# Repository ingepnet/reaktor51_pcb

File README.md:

# Reaktor51 kretskort for loddeøving

# #1 Reaktor51 LED

# #2 Reaktor51 Memory Game

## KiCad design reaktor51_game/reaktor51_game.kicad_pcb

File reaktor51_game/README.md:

# Reaktor51 Memory Game

Her er kort #2 i "Reaktor51" serien! Litt flere komponenter å lodde opp, men alt er enkle hullmonterte komponenter. Dette er et minnespill, der målet er å huske møsteret som blir vist med lyd og lys. Knappene har innebygde LED's som blinker i en tilfeldig rekkefølge. Spilleren må herme dette mønsteret ved å trykke på knappene. Lyd og lys indikerer om spilleren har tapt eller vunnet!

Det er valgt å bruke knapper med røde LED's. Disse lyser sterkest av de fargene som var tilgjengelig for denne typen knapper.

## Kretskort

Gerber for bestilling av PCB:
[./rev2/reaktor51_game_pcb_rev2.zip](./rev2/reaktor51_game_pcb_rev2.zip)

 - Loddestopplakk: Rød
 - Silketrykk: Hvit
 - Tykkelse: 1.6mm
 - Overflate: HASL lead free

## Deleliste

| Komponent | Beskrivelse                              | Antall   | Verdi           | Link   |
|-|-|-|-|-|
| BT1       | Batteriholder for CR2032                 | 1        | Keystone 103    | https://www.digikey.no/en/products/detail/keystone-electronics/103/331620       | 
| U1        | AVR Microkontroller                      | 1        | ATtiny13A-PU    | https://www.digikey.no/en/products/detail/microchip-technology/ATTINY13A-PU/1914671       | 
| C1, C2    | Keramisk kondensator                     | 2        | 1uF 25V         | https://www.digikey.no/en/products/detail/tdk-corporation/FG18X7R1E105KRT00/7326658      |
| LS1       | Piezo høyttaler D=14mm H=4mm Pitch=7.5mm | 1        | 14x4mm 7.5mm    | https://www.aliexpress.com/item/1005004932492920.html    |
| R1, R2, R3, R4, R6  | Motstand 150ohm (2.3x6mm)      | 5        | 150ohm          | https://www.digikey.no/en/products/detail/stackpole-electronics-inc/CF14JT150R/1741294    |
| R5        | Motstand 4.7kohm (2.3x6mm)               | 1        | 4.7kohm         | https://www.digikey.no/en/products/detail/stackpole-electronics-inc/CF14JT4K70/1741428    |
| SW1, SW2, SW3, SW4  | Trykknapp med rød LED 12x12mm  | 4        | 12x12x7.3 RED   | https://www.aliexpress.com/item/1005003507477622.html    |

## Skjema

## Håndtak

Bruk denne filen for å 3d-printe et håndtak, som gjør kortet behagelig å holde i. Printes i normal og speilvendt utgave. Klipp komponentbeina korte på undersiden, slik at håndtakene blir enklere å skyve innpå.

[./rev2/reaktor51_game_handle.step](./rev2/reaktor51_game_handle.step)

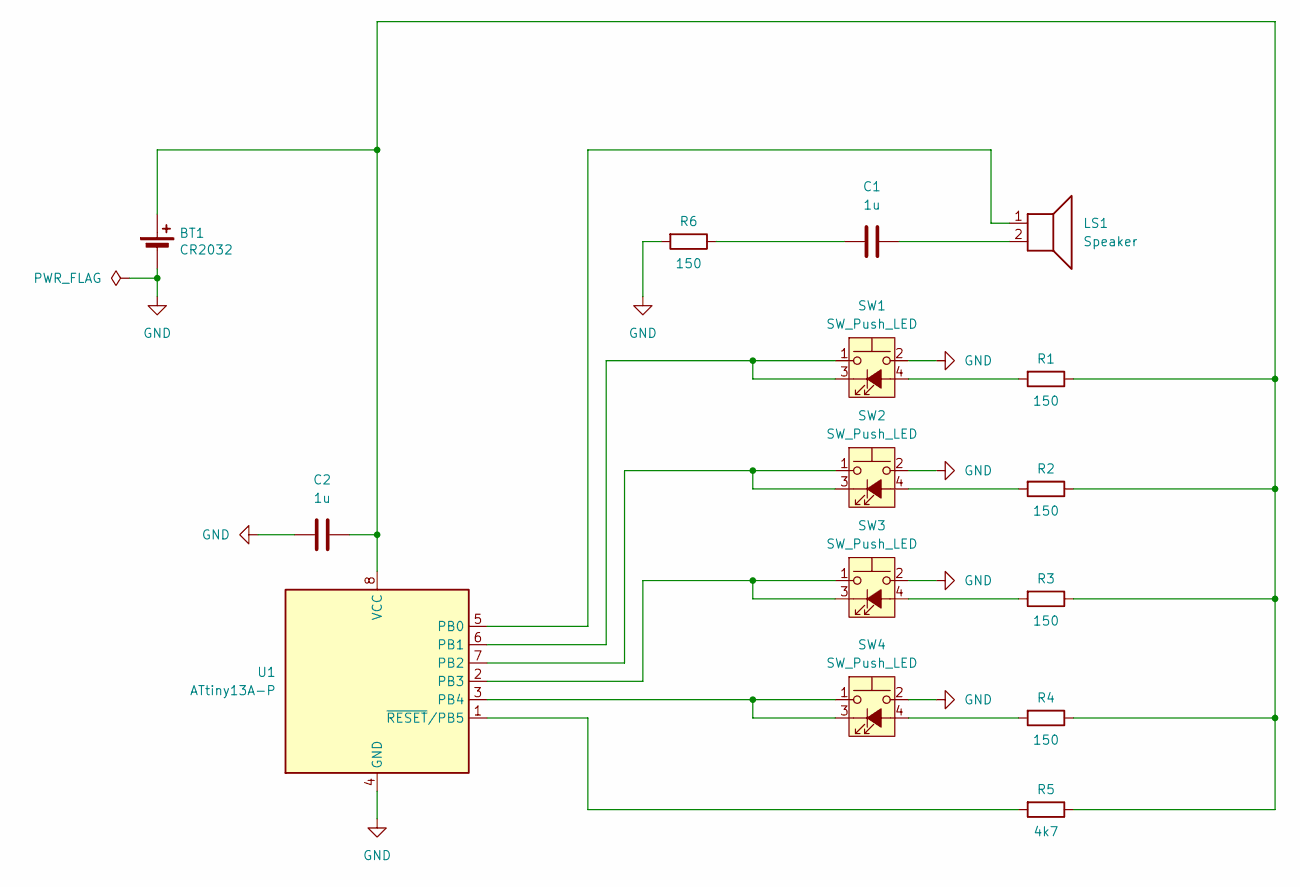
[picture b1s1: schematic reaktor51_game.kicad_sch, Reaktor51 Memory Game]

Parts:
BT1: CR2032; BatteryHolder_Keystone_103_1x20mm
C1, C2: 1u; C_Rect_L4.6mm_W3.0mm_P2.50mm_MKS02_FKP02
LS1: Speaker; Buzzer_15x7.5RM7.6
R1, R2, R3, R4, R6: 150; R_Axial_DIN0207_L6.3mm_D2.5mm_P10.16mm_Horizontal
R5: 4k7; R_Axial_DIN0207_L6.3mm_D2.5mm_P10.16mm_Horizontal
SW1, SW2, SW3, SW4: SW_Push_LED; SW_PUSH_12mm_LED
U1: ATtiny13A-P; DIP-8_W7.62mm

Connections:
GND: BT1.2 (-), C2.1, R6.2, SW1.2, SW2.2, SW3.2, SW4.2, U1.4 (GND)
unnamed: BT1.1 (+), C2.2, R1.1, R2.1, R3.1, R4.1, R5.1, U1.8 (VCC)
unnamed: C1.1, R6.1
unnamed: C1.2, LS1.2
unnamed: R1.2, SW1.4 (A)
unnamed: SW1.1, SW1.3 (K), U1.6 (PB1)
unnamed: R2.2, SW2.4 (A)
unnamed: SW2.1, SW2.3 (K), U1.7 (PB2)
unnamed: R3.2, SW3.4 (A)
unnamed: SW3.1, SW3.3 (K), U1.2 (PB3)
unnamed: R4.2, SW4.4 (A)
unnamed: SW4.1, SW4.3 (K), U1.3 (PB4)
unnamed: LS1.1, U1.5 (PB0)
unnamed: R5.2, U1.1 (~RESET/PB5)

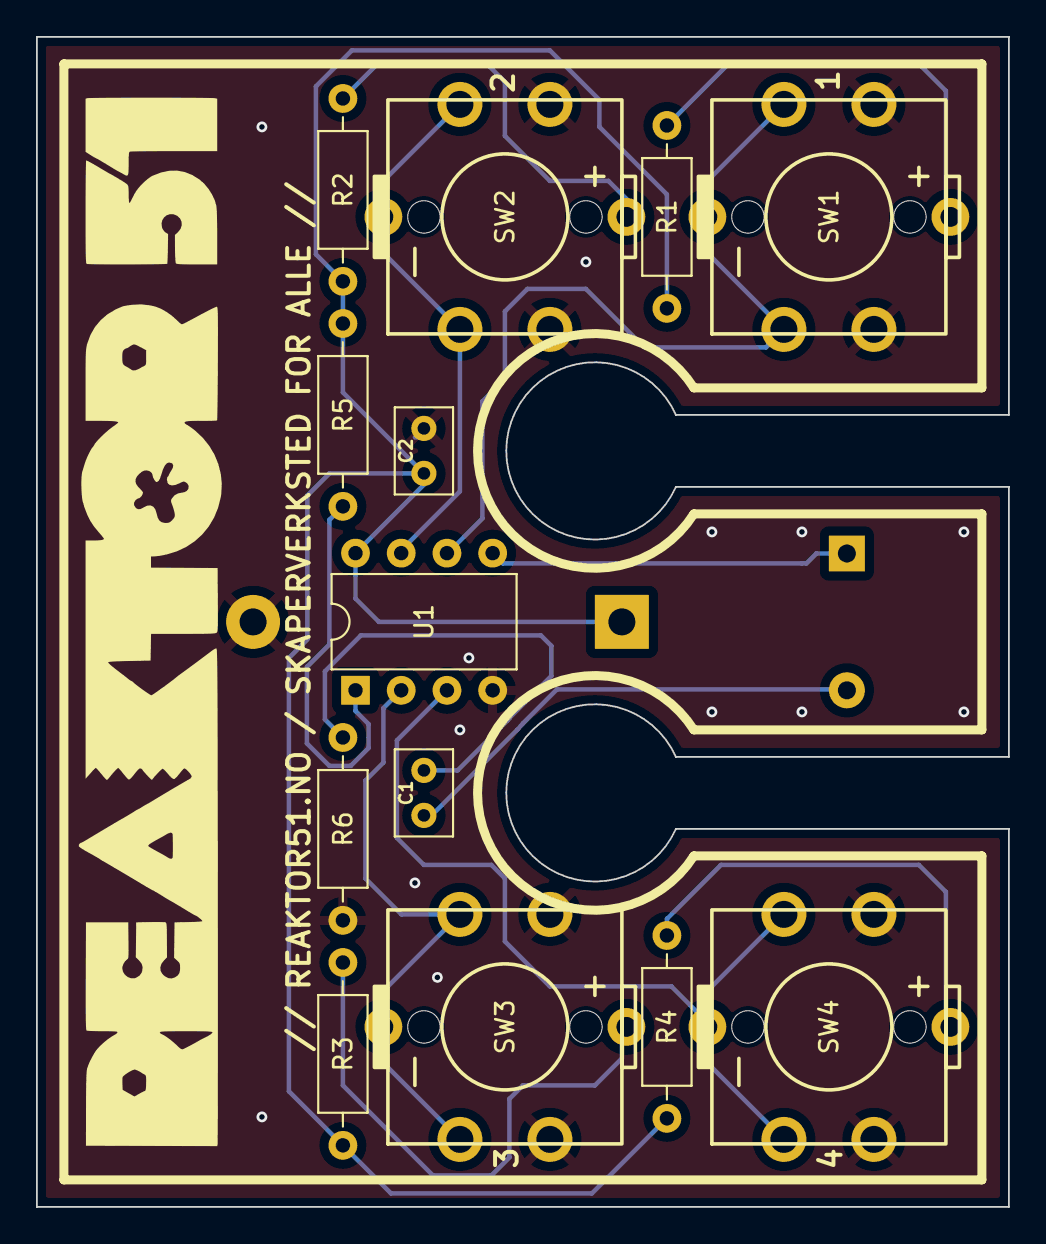
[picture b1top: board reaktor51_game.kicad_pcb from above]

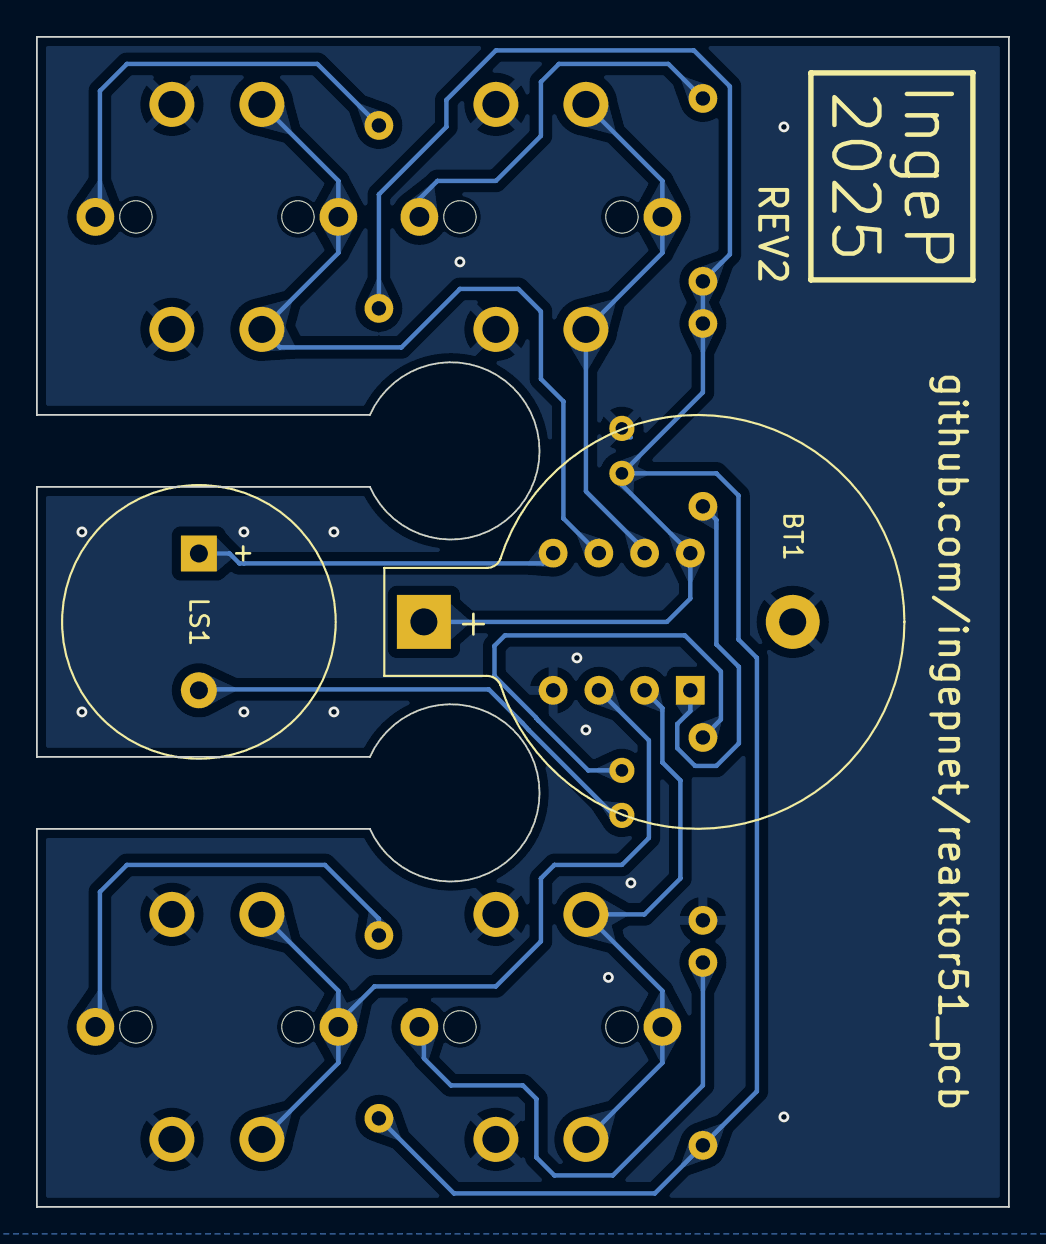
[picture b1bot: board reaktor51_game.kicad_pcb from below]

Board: 2 copper layers, 54.0 x 65.0 mm, 15 parts (2 on the bottom side), 14 nets.

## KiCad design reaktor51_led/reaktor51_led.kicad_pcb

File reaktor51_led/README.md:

# Reaktor51 LED PCB

Her er et enkelt design som intro til KiCad. Kortet egner seg også som et øvingskort for lodding.

Gerber for bestilling av PCB:
[out/reaktor51_led_rev1-rc2.zip](out/reaktor51_led_rev1-rc2.zip)

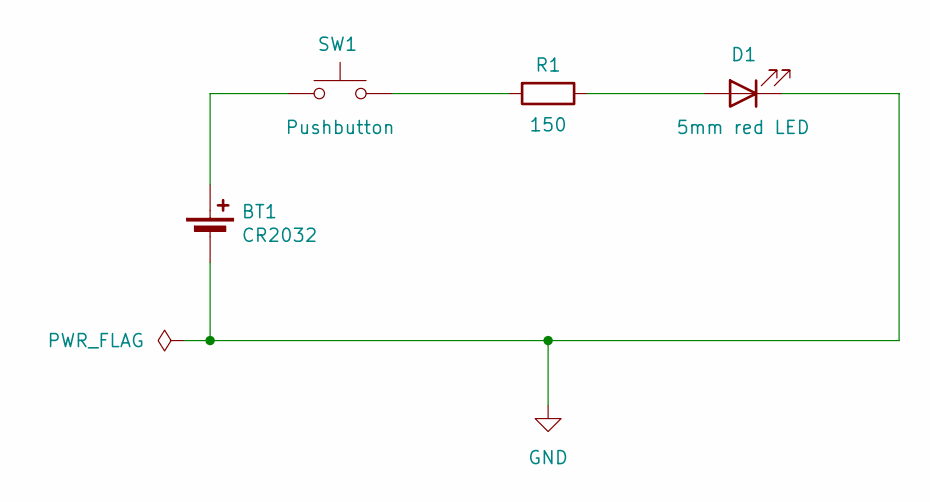
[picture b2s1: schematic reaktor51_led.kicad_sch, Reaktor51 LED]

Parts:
BT1: CR2032; BatteryHolder_Keystone_103_1x20mm; Digikey 36-103-ND
D1: 5mm red LED; LED_D5.0mm; Digikey 754-1277-ND
R1: 150; R_Axial_DIN0207_L6.3mm_D2.5mm_P10.16mm_Horizontal; Digikey CF14JT150RCT-ND
SW1: Pushbutton; SW_PUSH_6mm

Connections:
GND: BT1.2 (-), D1.1 (K)
unnamed: BT1.1 (+), SW1.1
unnamed: D1.2 (A), R1.1
unnamed: R1.2, SW1.2

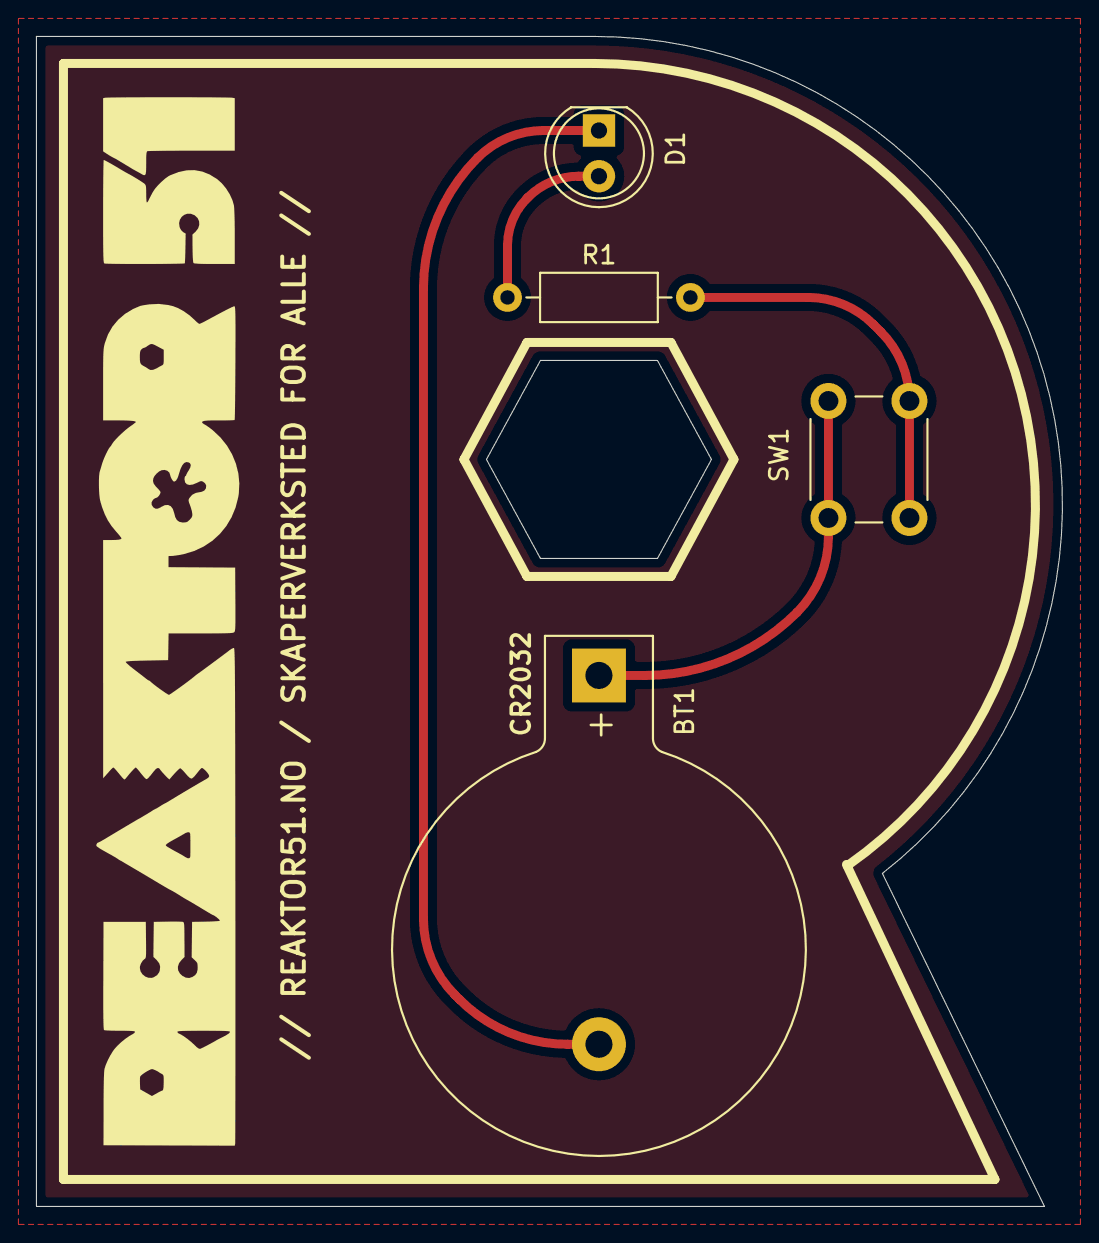
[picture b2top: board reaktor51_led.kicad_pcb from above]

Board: 2 copper layers, 57.0 x 65.0 mm, 4 parts (0 on the bottom side), 4 nets.

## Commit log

2024-04-12 REV1 - pcbway 11.04.2024
2024-04-15 Move to subfolder
2024-04-26 reaktor51_led rev1 rc2
2024-11-17 Reaktor51 Reaction Game REV1
2025-09-09 REV1 RC1 PCBWay
2025-09-10 Reaktor51 Memory Game REV2
2025-09-10 Front page README
2025-09-10 Add game handle
2025-09-12 Fixed typo in BOM
